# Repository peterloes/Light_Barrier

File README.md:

# Light barriers

A standalone platform for animal observation and manipulation.

This program is a software module for the hardware platform
"Light_Barrier_2015_3" developed for two pairs of lightbarriers.

Wide Input Voltage Range: 3.3V to 60V

Example with receiver from Vishay: TSSP58038 and LED Vishay: VSLB3940

Always low level triggered for wire monitoring(breakage).

Two high level signal: 204µA@3,3V  -- Two low  level signal: 1.49mA@3,3V

Two high level signal: 195µA@5V    -- Two low  level signal: 1.49mA@5V

Two high level signal: 195µA@13,2V -- Two low  level signal: 1.47mA@13,2V

Parameter distance 3,3 Meter: 4mA@12V average

Prototype: Bat counter 

The distance from light barrier 1 is 15cm and from light barrier 2 is 13cm.

https://github.com/peterloes/Light_Barrier/blob/master/Getting_Started_Tutorial/1_poster_overview_LightBarrier_Counter.pdf

Prototype: Long range RFID- reader for shore birds

https://github.com/peterloes/Light_Barrier/blob/master/Getting_Started_Tutorial/1_poster_overview_MOMO_LB_LR.pdf

Mainboard:

https://github.com/peterloes/MOMO

https://github.com/peterloes/RFID-MS

Manufacture:

https://github.com/peterloes/Light_Barrier/blob/master/Getting_Started_Tutorial/3_Supplier.txt

EXTENSION:

https://github.com/peterloes/SmartAnimalTraps

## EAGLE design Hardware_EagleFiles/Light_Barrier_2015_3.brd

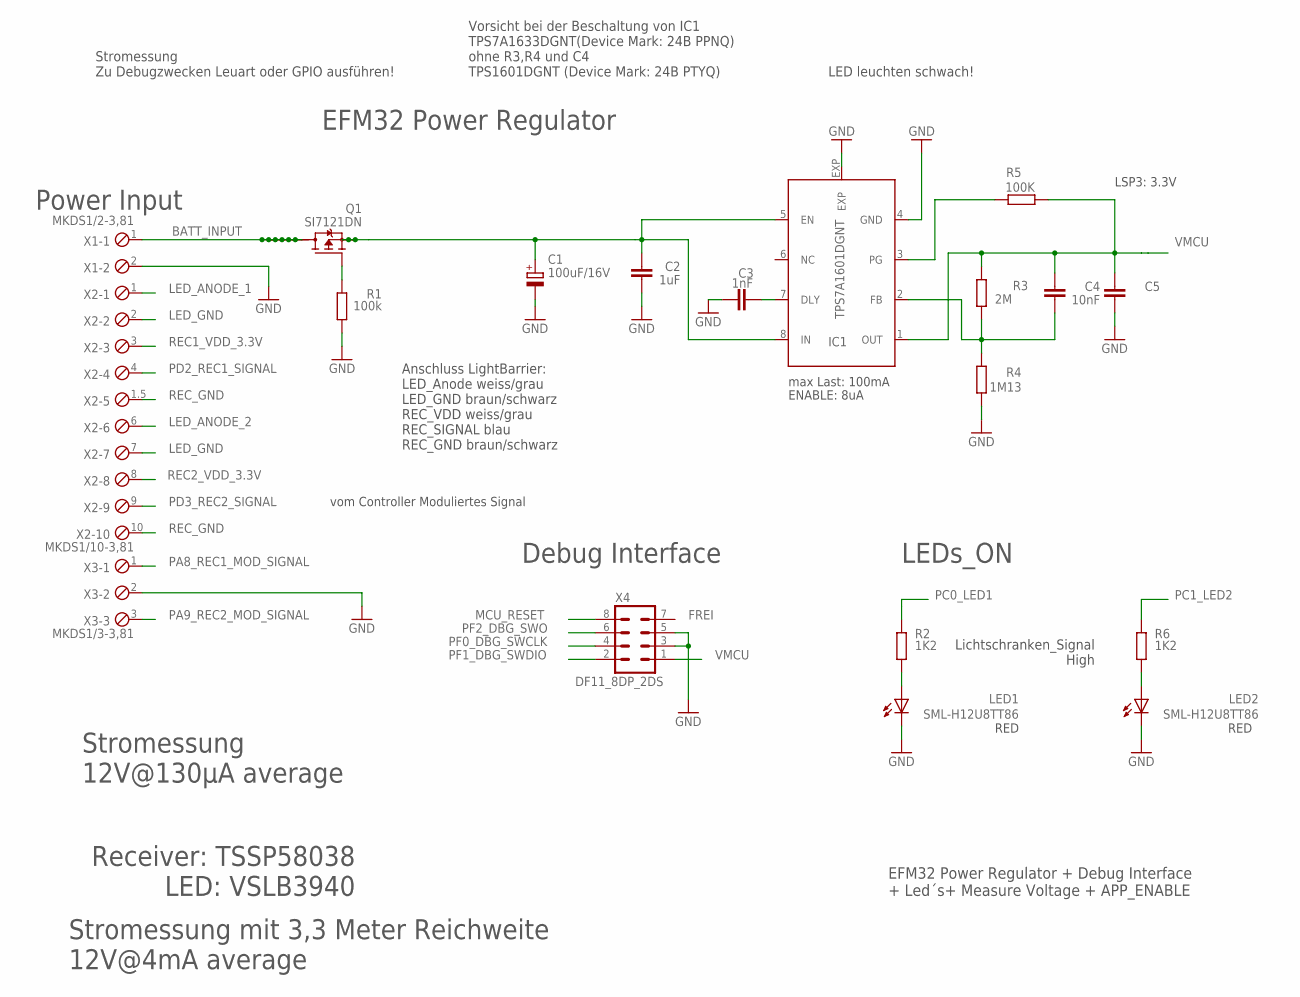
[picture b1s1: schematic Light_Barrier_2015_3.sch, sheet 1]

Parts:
C1: 100uF/16V; PANASONIC_E
C2: 1uF; C0603
C3: 1nF; C0603
C4: 10nF; C0603
C5: 10uF; C1206
IC1: TPS7A1601DGNT; DGN_S-PDSO-G8-EXP
LED1, LED2: SML-H12U8TT86; CHIPLED_0805
Q1: SI7121DN; TRANSISTOR-FET_1212-8S
R1: 100k; R0805
R2, R6: 1K2; R0805
R3: 2M; R0805
R4: 1M13; R0805
R5: 100K; R0805
X1: MKDS1/2-3,81; 2POL381
X2: MKDS1/10-3,81; 10POL381
X3: MKDS1/3-3,81; 3POL381
X4: DF11_8DP_2DS; DP11_8DP-2DS

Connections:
BATT_INPUT: Q1.5 (D), Q1.6 (D), Q1.7 (D), Q1.8 (D), Q1.9 (D), Q1.10 (D), Q1.11 (D), X1.1
GND: C1.-, C2.1, C3.1, C5.1, IC1.4 (GND), IC1.EXP, LED1.C, LED2.C, R1.1, R4.1, X1.2, X3.2, X4.3, X4.5; also elsewhere on the board
LED_ANODE_1: X2.1; also elsewhere on the board
LED_ANODE_2: X2.6; also elsewhere on the board
LED_GND: X2.2, X2.7; also elsewhere on the board
MCU_RESET: X4.8; also elsewhere on the board
unnamed: C4.1, IC1.2 (FB), R3.1, R4.2
unnamed: C3.2, IC1.7 (DLY)
unnamed: C1.+, C2.2, IC1.5 (EN), IC1.8 (IN), Q1.1 (S), Q1.2 (S), Q1.3 (S)
unnamed: IC1.3 (PG), R5.2
unnamed: Q1.4 (G), R1.2
unnamed: LED1.A, R2.2
unnamed: LED2.A, R6.2
PA8_REC1_MOD_SIGNAL: X3.1; also elsewhere on the board
PA9_REC2_MOD_SIGNAL: X3.3; also elsewhere on the board
PC0_LED1: R2.1; also elsewhere on the board
PC1_LED2: R6.1; also elsewhere on the board
PD2_REC1_SIGNAL: X2.4; also elsewhere on the board
PD3_REC2_SIGNAL: X2.9; also elsewhere on the board
PF0_DBG_SWCLK: X4.4; also elsewhere on the board
PF1_DBG_SWDIO: X4.2; also elsewhere on the board
PF2_DBG_SWO: X4.6; also elsewhere on the board
REC1_VDD_3.3V: X2.3; also elsewhere on the board
REC2_VDD_3.3V: X2.8; also elsewhere on the board
REC_GND: X2.1.5, X2.10; also elsewhere on the board
VMCU: C4.2, C5.2, IC1.1 (OUT), R3.2, R5.1, X4.1; also elsewhere on the board

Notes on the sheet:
EFM32 Power Regulator + Debug Interface + Led´s+ Measure Voltage + APP_ENABLE
ENABLE: 8uA
Power Input
max Last: 100mA
LSP3: 3.3V
EFM32 Power Regulator
Debug Interface
LEDs_ON
FREI
RED
Receiver: TSSP58038 LED: VSLB3940
Lichtschranken_Signal High
vom Controller Moduliertes Signal
Stromessung 12V@130µA average
Stromessung mit 3,3 Meter Reichweite 12V@4mA average
Stromessung Zu Debugzwecken Leuart oder GPIO ausführen!
Vorsicht bei der Beschaltung von IC1 TPS7A1633DGNT(Device Mark: 24B PPNQ) ohne R3,R4 und C4 TPS1601DGNT (Device Mark: 24B PTYQ)
LED leuchten schwach!
Anschluss LightBarrier: LED_Anode weiss/grau LED_GND braun/schwarz REC_VDD weiss/grau REC_SIGNAL blau REC_GND braun/schwarz

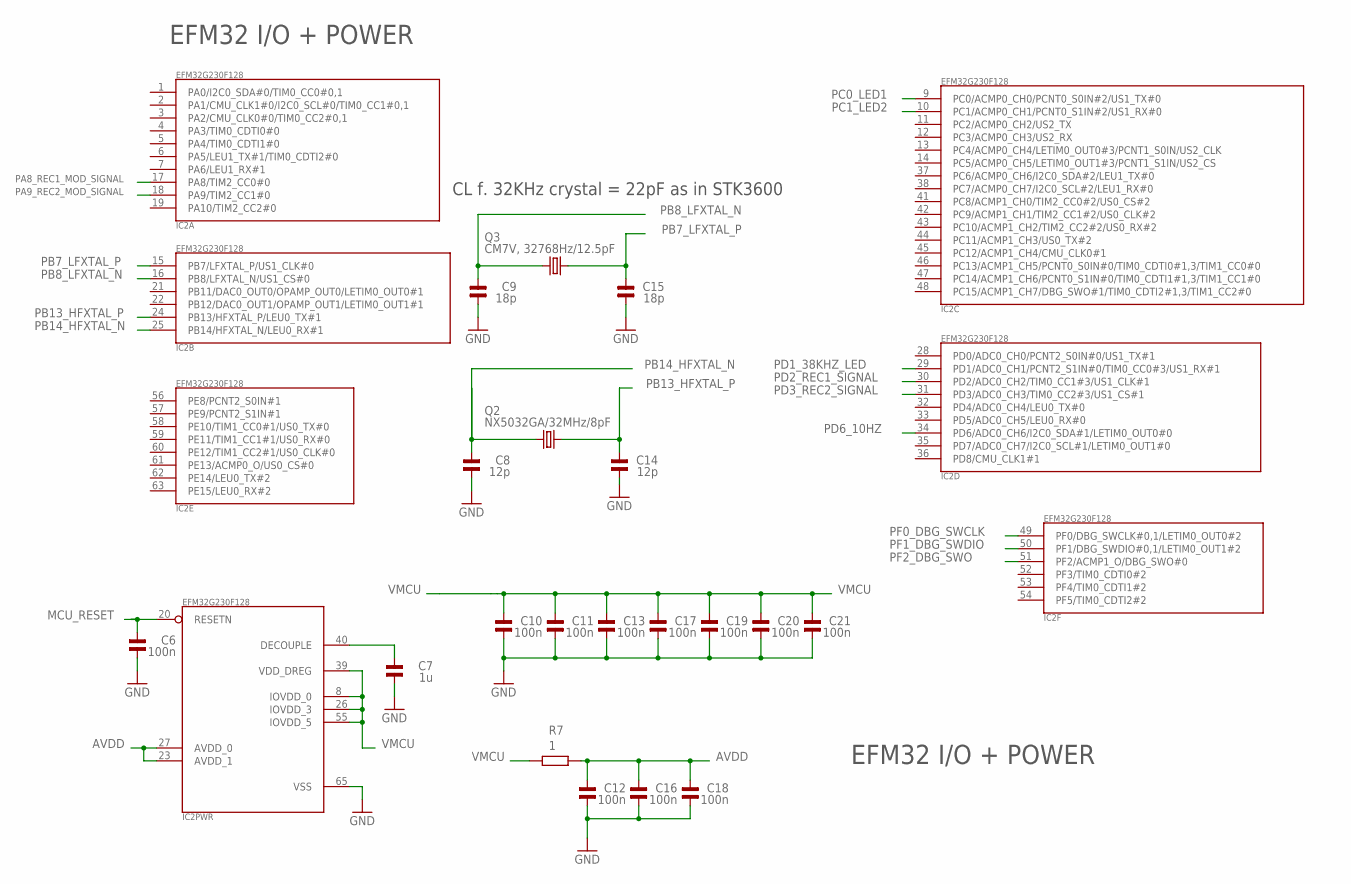
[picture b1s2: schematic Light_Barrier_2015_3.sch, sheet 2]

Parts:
C6, C10, C11, C12, C13, C16, C17, C18, C19, C20, C21: 100n; 0805
C7: 1u; 0805
C8, C14: 12p; 0805
C9, C15: 18p; 0805
IC2: EFM32G230F128; QFN64
Q2: NX5032GA/32MHz/8pF; CRYSTAL2P5.0X3.2
Q3: CM7V, 32768Hz/12.5pF; CRYSTAL2P3.2X1.5
R7: 1; R0805

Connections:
AVDD: C12.2, C16.2, C18.2, IC2.23 (AVDD_1), IC2.27 (AVDD_0), R7.2
GND: C6.1, C7.1, C8.1, C9.1, C10.1, C11.1, C12.1, C13.1, C14.1, C15.1, C16.1, C17.1, C18.1, C19.1, C20.1, C21.1, IC2.65 (VSS); also elsewhere on the board
MCU_RESET: C6.2, IC2.20 (RESETN); also elsewhere on the board
unnamed: C7.2, IC2.40 (DECOUPLE)
PA8_REC1_MOD_SIGNAL: IC2.17 (PA8/TIM2_CC0#0); also elsewhere on the board
PA9_REC2_MOD_SIGNAL: IC2.18 (PA9/TIM2_CC1#0); also elsewhere on the board
PB7_LFXTAL_P: C15.2, IC2.15 (PB7/LFXTAL_P/US1_CLK#0), Q3.2
PB8_LFXTAL_N: C9.2, IC2.16 (PB8/LFXTAL_N/US1_CS#0), Q3.1
PB13_HFXTAL_P: C14.2, IC2.24 (PB13/HFXTAL_P/LEU0_TX#1), Q2.2
PB14_HFXTAL_N: C8.2, IC2.25 (PB14/HFXTAL_N/LEU0_RX#1), Q2.1
PC0_LED1: IC2.9 (PC0/ACMP0_CH0/PCNT0_S0IN#2/US1_TX#0); also elsewhere on the board
PC1_LED2: IC2.10 (PC1/ACMP0_CH1/PCNT0_S1IN#2/US1_RX#0); also elsewhere on the board
PD1_38KHZ_LED: IC2.29 (PD1/ADC0_CH1/PCNT2_S1IN#0/TIM0_CC0#3/US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); also elsewhere on the board
PD2_REC1_SIGNAL: IC2.30 (PD2/ADC0_CH2/TIM0_CC1#3/US1_CLK#1); also elsewhere on the board
PD3_REC2_SIGNAL: IC2.31 (PD3/ADC0_CH3/TIM0_CC2#3/US1_CS#1); also elsewhere on the board
PD6_10HZ: IC2.34 (PD6/ADC0_CH6/I2C0_SDA#1/LETIM0_OUT0#0); also elsewhere on the board
PF0_DBG_SWCLK: IC2.49 (PF0/DBG_SWCLK#0,1/LETIM0_OUT0#2); also elsewhere on the board
PF1_DBG_SWDIO: IC2.50 (PF1/DBG_SWDIO#0,1/LETIM0_OUT1#2); also elsewhere on the board
PF2_DBG_SWO: IC2.51 (PF2/ACMP1_O/DBG_SWO#0); also elsewhere on the board
VMCU: C10.2, C11.2, C13.2, C17.2, C19.2, C20.2, C21.2, IC2.8 (IOVDD_0), IC2.26 (IOVDD_3), IC2.39 (VDD_DREG), IC2.55 (IOVDD_5), R7.1; also elsewhere on the board

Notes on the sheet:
EFM32 I/O + POWER
CL f. 32KHz crystal = 22pF as in STK3600

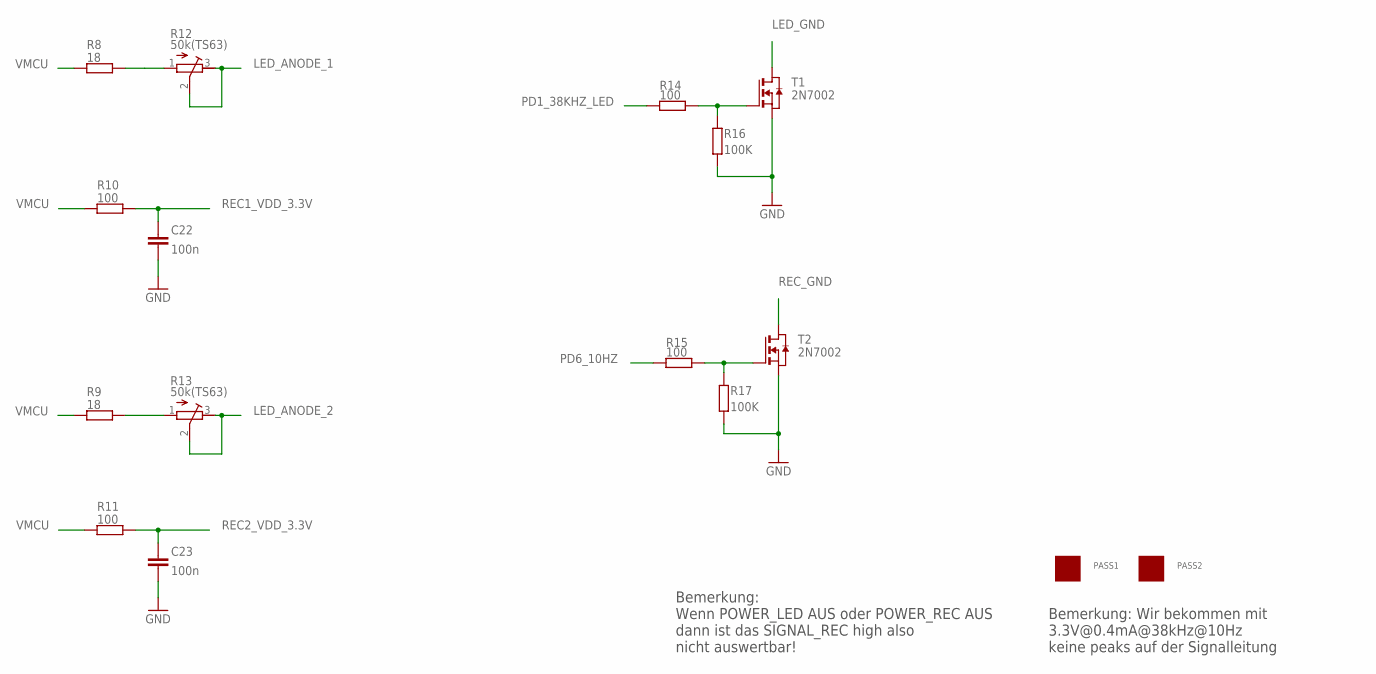
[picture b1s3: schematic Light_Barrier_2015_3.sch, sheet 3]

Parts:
C22, C23: 100n; C0805
PASS1, PASS2: ROUND_1MM1.5; ROUND2_1.5MM
R8, R9: 18; R0805
R10, R11, R14, R15: 100; R0805
R12, R13: 50k(TS63); RTRIMTS63Y
R16, R17: 100K; R0805
T1, T2: 2N7002; ZETEX_SOT-23

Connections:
GND: C22.2, C23.2, R16.1, R17.1, T1.2 (S), T2.2 (S); also elsewhere on the board
LED_ANODE_1: R12.2 (S), R12.3 (E); also elsewhere on the board
LED_ANODE_2: R13.2 (S), R13.3 (E); also elsewhere on the board
LED_GND: T1.1 (D); also elsewhere on the board
unnamed: R9.2, R13.1 (A)
unnamed: R8.2, R12.1 (A)
unnamed: R14.1, R16.2, T1.3 (G)
unnamed: R15.1, R17.2, T2.3 (G)
PD1_38KHZ_LED: R14.2; also elsewhere on the board
PD6_10HZ: R15.2; also elsewhere on the board
REC1_VDD_3.3V: C22.1, R10.2; also elsewhere on the board
REC2_VDD_3.3V: C23.1, R11.2; also elsewhere on the board
REC_GND: T2.1 (D); also elsewhere on the board
VMCU: R8.1, R9.1, R10.1, R11.1; also elsewhere on the board

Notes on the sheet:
Bemerkung: Wir bekommen mit 3.3V@0.4mA@38kHz@10Hz keine peaks auf der Signalleitung
Bemerkung: Wenn POWER_LED AUS oder POWER_REC AUS dann ist das SIGNAL_REC high also nicht auswertbar!

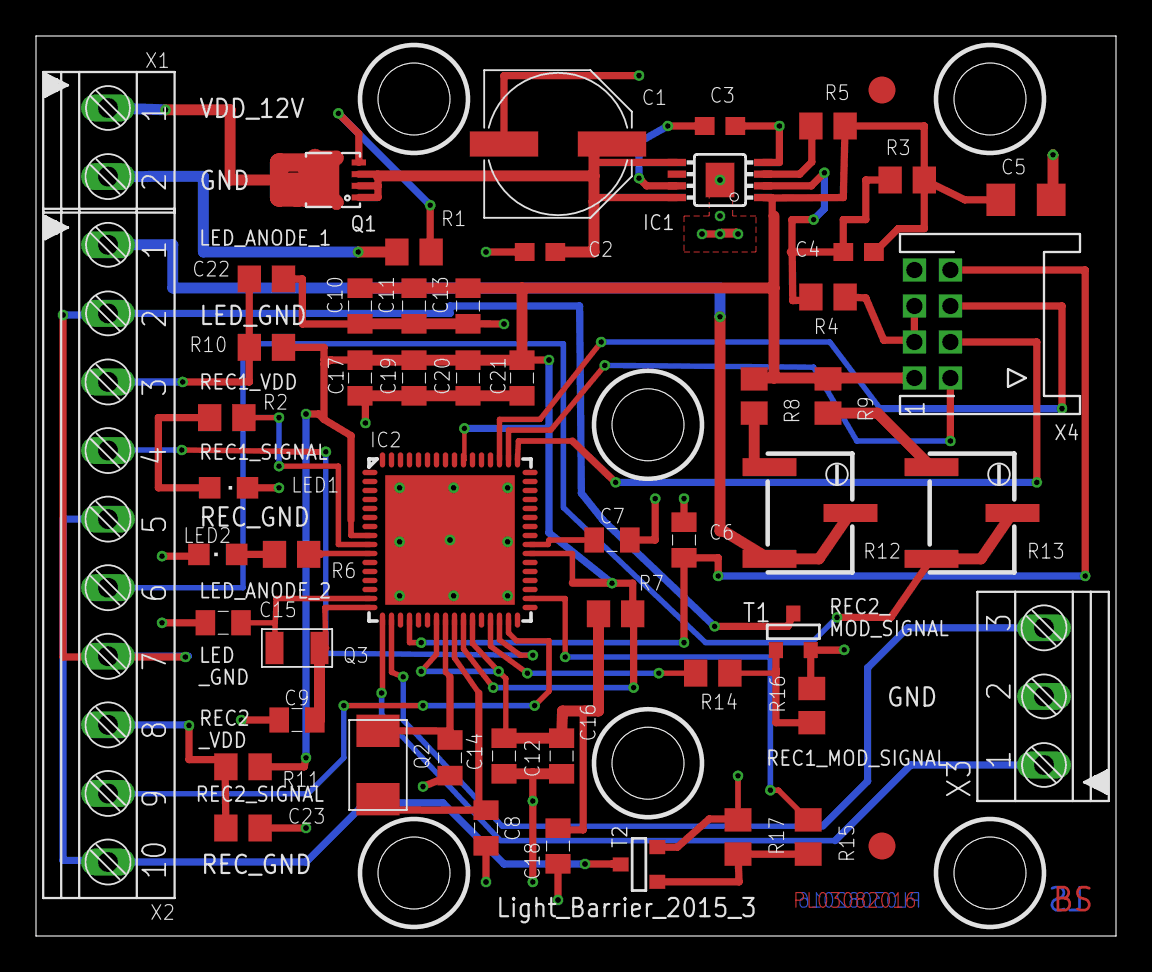
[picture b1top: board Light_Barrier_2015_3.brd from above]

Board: 4 copper layers, 60.0 x 50.0 mm, 55 parts (0 on the bottom side), 38 nets.

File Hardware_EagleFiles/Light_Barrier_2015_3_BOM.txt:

Partlist exported from C:/MPIO/TECHNIK/HARDWARE/EAGLE_FILES/Light_Barrier_2015/Light_Barrier_2015_3.sch at 8/3/2016 8:29:31 AM

Part  Value                Device                  Package                Description                                                    
C1    100uF/16V            CPOL-EUE                PANASONIC_E            POLARIZED CAPACITOR, European symbol                           
C2    1uF                  C-EUC0603               C0603                  CAPACITOR, European symbol                                     
C3    1nF                  C-EUC0603               C0603                  CAPACITOR, European symbol                                     
C4    10nF                 C-EUC0603               C0603                  CAPACITOR, European symbol                                     
C5    10uF                 C-EUC1206               C1206                  CAPACITOR, European symbol                                     
C6    100n                 C_SMD0805               0805                                                                                  
C7    1u                   C_SMD0805               0805                                                                                  
C8    12p                  C_SMD0805               0805                                                                                  
C9    18p                  C_SMD0805               0805                                                                                  
C10   100n                 C_SMD0805               0805                                                                                  
C11   100n                 C_SMD0805               0805                                                                                  
C12   100n                 C_SMD0805               0805                                                                                  
C13   100n                 C_SMD0805               0805                                                                                  
C14   12p                  C_SMD0805               0805                                                                                  
C15   18p                  C_SMD0805               0805                                                                                  
C16   100n                 C_SMD0805               0805                                                                                  
C17   100n                 C_SMD0805               0805                                                                                  
C18   100n                 C_SMD0805               0805                                                                                  
C19   100n                 C_SMD0805               0805                                                                                  
C20   100n                 C_SMD0805               0805                                                                                  
C21   100n                 C_SMD0805               0805                                                                                  
C22   100n                 C-EUC0805               C0805                  CAPACITOR, European symbol                                     
C23   100n                 C-EUC0805               C0805                  CAPACITOR, European symbol                                     
IC1   TPS7A1601DGNT        TPS7A16                 DGN_S-PDSO-G8-EXP                                                                     
IC2   EFM32G230F128        EFM32G230F128           QFN64                  EFM32G230F128 Gecko Microcontroller in 9mm x 9mm QFN64 package 
LED1  SML-211UT            LEDCHIPLED_0805         CHIPLED_0805           LED                                                            
LED2  SML-211UT            LEDCHIPLED_0805         CHIPLED_0805           LED                                                            
PASS1 ROUND_1MM1.5         ROUND_1MM1.5            ROUND2_1.5MM                                                                          
PASS2 ROUND_1MM1.5         ROUND_1MM1.5            ROUND2_1.5MM                                                                          
Q1    SI7121DN             TRANSISTOR-FET_SI7113DN TRANSISTOR-FET_1212-8S                                                                
Q2    NX5032GA/32MHz/8pF   CRYSTAL2P5.0X3.2        CRYSTAL2P5.0X3.2       Quarz Crystal                                                  
Q3    CM7V, 32768Hz/12.5pF CRYSTAL2P               CRYSTAL2P3.2X1.5       Quarz Crystal                                                  
R1    100k                 R-EU_R0805              R0805                  RESISTOR, European symbol                                      
R2    1K2                  R-EU_R0805              R0805                  RESISTOR, European symbol                                      
R3    2M                   R-EU_R0805              R0805                  RESISTOR, European symbol                                      
R4    1M13                 R-EU_R0805              R0805                  RESISTOR, European symbol                                      
R5    100K                 R-EU_R0805              R0805                  RESISTOR, European symbol                                      
R6    1K2                  R-EU_R0805              R0805                  RESISTOR, European symbol                                      
R7    1                    R-EU_R0805              R0805                  RESISTOR, European symbol                                      
R8    18                   R-EU_R0805              R0805                  RESISTOR, European symbol                                      
R9    18                   R-EU_R0805              R0805                  RESISTOR, European symbol                                      
R10   100                  R-EU_R0805              R0805                  RESISTOR, European symbol                                      
R11   100                  R-EU_R0805              R0805                  RESISTOR, European symbol                                      
R12   50k(TS63)            R-TRIMMTS63Y            RTRIMTS63Y             Trimm resistor                                                 
R13   50k(TS63)            R-TRIMMTS63Y            RTRIMTS63Y             Trimm resistor                                                 
R14   100                  R-EU_R0805              R0805                  RESISTOR, European symbol                                      
R15   100                  R-EU_R0805              R0805                  RESISTOR, European symbol                                      
R16   100K                 R-EU_R0805              R0805                  RESISTOR, European symbol                                      
R17   100K                 R-EU_R0805              R0805                  RESISTOR, European symbol                                      
T1    2N7002               ZETEX_NMOSSOT23         ZETEX_SOT-23           MOS FET                                                        
T2    2N7002               ZETEX_NMOSSOT23         ZETEX_SOT-23           MOS FET                                                        
X1    MKDS1/2-3,81         MKDS1/2-3,81            2POL381                MKDS 1/2-3,81 - Order No. 1727010 (RS-Online - 101-5384)       
X2    MKDS1/10-3,81        MKDS1/10-3,81           10POL381               MKDS 1/10-3,81 - Order No. 1727094                             
X3    MKDS1/3-3,81         MKDS1/3-3,81            3POL381                MKDS 1/3-3,81 - Order No. 1727023 (RS-Online - 101-5390)       
X4    DF11_8DP_2DS         DP11_8DP_2DS            DP11_8DP-2DS

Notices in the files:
parts and their libraries:
EnergyMicro: CC0 License
SparkFun-Aesthetics: Licensing: CC v3.0 Share-Alike You are welcome to use this library for commercial purposes.
